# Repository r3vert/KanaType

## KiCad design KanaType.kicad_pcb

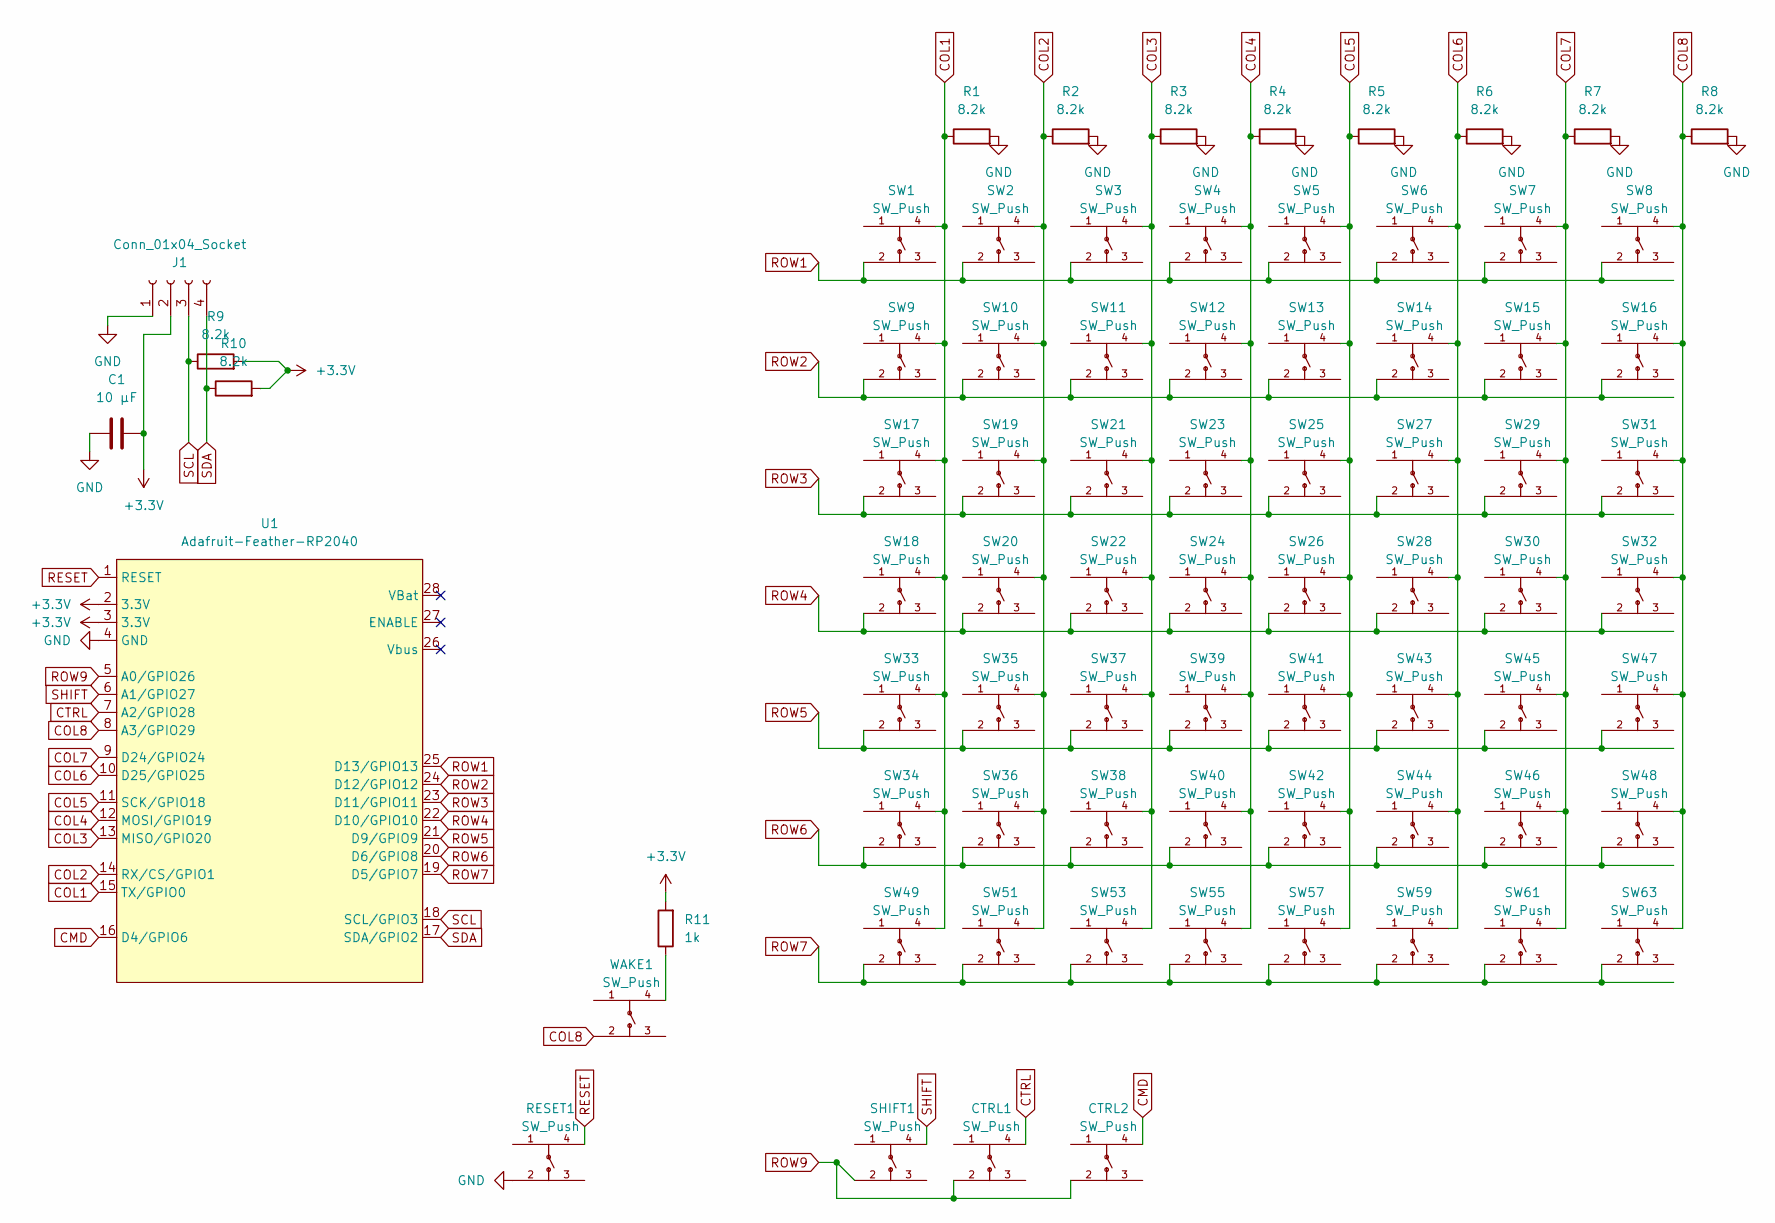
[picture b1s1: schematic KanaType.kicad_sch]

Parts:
C1: 10 μF; C_0805_2012Metric_Pad1.18x1.45mm_HandSolder
CTRL1, CTRL2: SW_Push; SW-SMD_4P-L4.2-W3.2-P2.15-LS4.6; LCSC C2910644
J1: Conn_01x04_Socket; PinSocket_1x04_P2.54mm_Vertical
R1, R2, R3, R4, R5, R6, R7, R8, R9, R10: 8.2k; R_0805_2012Metric_Pad1.20x1.40mm_HandSolder
R11: 1k; R_0805_2012Metric_Pad1.20x1.40mm_HandSolder
RESET1: SW_Push; SW-SMD_4P-L4.2-W3.2-P2.15-LS4.6; LCSC C2910644
SHIFT1: SW_Push; SW-SMD_4P-L4.2-W3.2-P2.15-LS4.6; LCSC C2910644
SW1, SW2, SW3, SW4, SW5, SW6, SW7, SW8, SW9, SW10, SW11, SW12, SW13, SW14, SW15, SW16, SW17, SW18, SW19, SW20, SW21, SW22, SW23, SW24, SW25, SW26, SW27, SW28, SW29, SW30, SW31, SW32, SW33, SW34, SW35, SW36, SW37, SW38, SW39, SW40, SW41, SW42, SW43, SW44, SW45, SW46, SW47, SW48, SW49, SW51, SW53, SW55, SW57, SW59, SW61, SW63: SW_Push; SW-SMD_4P-L4.2-W3.2-P2.15-LS4.6; LCSC C2910644
U1: Adafruit-Feather-RP2040; Adafruit_Feather
WAKE1: SW_Push; SW-SMD_4P-L4.2-W3.2-P2.15-LS4.6; LCSC C2910644

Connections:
+3.3V: C1.2, J1.2, R9.2, R10.2, R11.2, U1.2 (3.3V), U1.3 (3.3V)
CMD: CTRL2.4, U1.16 (D4/GPIO6)
COL1: R1.1, SW1.4, SW9.4, SW17.4, SW18.4, SW33.4, SW34.4, SW49.4, U1.15 (TX/GPIO0)
COL2: R2.1, SW2.4, SW10.4, SW19.4, SW20.4, SW35.4, SW36.4, SW51.4, U1.14 (RX/CS/GPIO1)
COL3: R3.1, SW3.4, SW11.4, SW21.4, SW22.4, SW37.4, SW38.4, SW53.4, U1.13 (MISO/GPIO20)
COL4: R4.1, SW4.4, SW12.4, SW23.4, SW24.4, SW39.4, SW40.4, SW55.4, U1.12 (MOSI/GPIO19)
COL5: R5.1, SW5.4, SW13.4, SW25.4, SW26.4, SW41.4, SW42.4, SW57.4, U1.11 (SCK/GPIO18)
COL6: R6.1, SW6.4, SW14.4, SW27.4, SW28.4, SW43.4, SW44.4, SW59.4, U1.10 (D25/GPIO25)
COL7: R7.1, SW7.4, SW15.4, SW29.4, SW30.4, SW45.4, SW46.4, SW61.4, U1.9 (D24/GPIO24)
COL8: R8.1, SW8.4, SW16.4, SW31.4, SW32.4, SW47.4, SW48.4, SW63.4, U1.8 (A3/GPIO29), WAKE1.2
CTRL: CTRL1.4, U1.7 (A2/GPIO28)
GND: C1.1, J1.1, R1.2, R2.2, R3.2, R4.2, R5.2, R6.2, R7.2, R8.2, RESET1.2, U1.4 (GND)
unnamed: R11.1, WAKE1.4
RESET: RESET1.4, U1.1 (RESET)
ROW1: SW1.2, SW2.2, SW3.2, SW4.2, SW5.2, SW6.2, SW7.2, SW8.2, U1.25 (D13/GPIO13)
ROW2: SW9.2, SW10.2, SW11.2, SW12.2, SW13.2, SW14.2, SW15.2, SW16.2, U1.24 (D12/GPIO12)
ROW3: SW17.2, SW19.2, SW21.2, SW23.2, SW25.2, SW27.2, SW29.2, SW31.2, U1.23 (D11/GPIO11)
ROW4: SW18.2, SW20.2, SW22.2, SW24.2, SW26.2, SW28.2, SW30.2, SW32.2, U1.22 (D10/GPIO10)
ROW5: SW33.2, SW35.2, SW37.2, SW39.2, SW41.2, SW43.2, SW45.2, SW47.2, U1.21 (D9/GPIO9)
ROW6: SW34.2, SW36.2, SW38.2, SW40.2, SW42.2, SW44.2, SW46.2, SW48.2, U1.20 (D6/GPIO8)
ROW7: SW49.2, SW51.2, SW53.2, SW55.2, SW57.2, SW59.2, SW61.2, SW63.2, U1.19 (D5/GPIO7)
ROW9: CTRL1.2, CTRL2.2, SHIFT1.2, U1.5 (A0/GPIO26)
SCL: J1.3, R9.1, U1.18 (SCL/GPIO3)
SDA: J1.4, R10.1, U1.17 (SDA/GPIO2)
SHIFT: SHIFT1.4, U1.6 (A1/GPIO27)

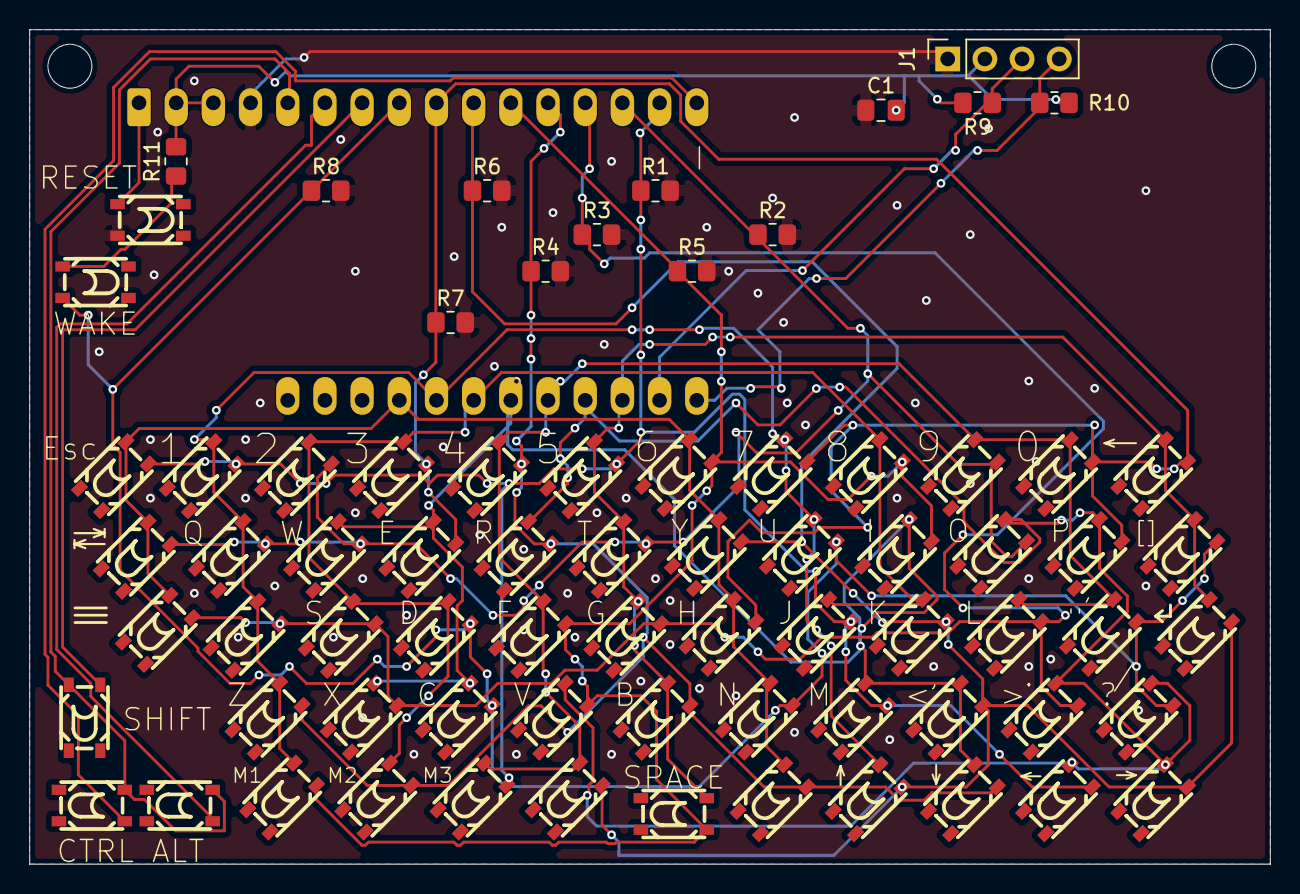
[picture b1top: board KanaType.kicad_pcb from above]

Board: 2 copper layers, 84.8 x 57.0 mm, 75 parts (1 on the bottom side), 25 nets.

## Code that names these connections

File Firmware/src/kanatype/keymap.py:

"""Physical keymap — single source of truth for BOTH the KMK keyboard app and
the app-platform MatrixInput driver (PLAN.md parity rule).

Grid derived from the PCB netlist + placement data (5 rows x 12 cols).
Each entry: (sw_ref, matrix_row 1-7, matrix_col 1-8, app_code, kmk_name)
  app_code: logical code for kanatype.input (None = no app meaning yet)
  kmk_name: attribute of kmk.keys.KC for USB keyboard mode

PROVISIONAL Preonic-style QWERTY — edit legends here and both worlds follow.
Hardware modifiers (CTRL1/CTRL2/SHIFT1) are off-matrix: see MOD_* below.
PURE PYTHON: no board imports (desktop renderer reads this file too).
"""

# Feather pin NAMES (resolved via getattr(board, name) on-device).
ROW_PIN_NAMES = ("D13", "D12", "D11", "D10", "D9", "D6", "D5")   # ROW1..ROW7
COL_PIN_NAMES = ("TX", "RX", "MISO", "MOSI", "SCK", "D25", "D24", "A3")  # COL1..COL8
ROW9_PIN_NAME = "A0"    # held LOW so modifiers read as ground-switched keys
# Hardware modifier keys by PCB net: A1=SHIFT1, A2=CTRL1, D4=CTRL2("CMD").
# USB functions remapped per user (2026-08): SHIFT1 key -> Alt,
# CTRL1 key -> Shift, CMD key -> Ctrl. No GUI key on this board.
MOD_PIN_NAMES = ("A1", "A2", "D4")
MOD_KMK_NAMES = ("LALT", "LSFT", "LCTL")

# MENU key (SW3, physically under Tab; was GRV). Holding it in keyboard mode
# returns to the launcher -- it replaced the Ctrl+Alt+Shift chord, which fired
# the instant all three went down and so could not be held deliberately.
# It sends NOTHING over USB ("NO"): the host repeats a held character, so a
# key you are meant to hold cannot also type one. In the apps it reads as
# "exit", the same code as ESC.
MENU_KEY = (1, 3)          # (matrix_row, matrix_col)

# User-assignable macro keys, left to right:
#     M1 = SW13 (2,5)   M2 = SW23 (3,4)   M3 = SW33 (5,1)   M4 = SW43 (5,6)
# Positions verified by matching silkscreen gr_text to footprint placement in
# KanaType.kicad_pcb. BOARD ERRATUM: the silkscreen prints M1/M2/M3 but has no
# legend for M4 (SW43) -- the key is unlabelled on the PCB, so the on-screen
# assignment list is the only place it is identified. Fix in v2.
# SW57 (7,5) is the spacebar and carries the SPACE legend, on its own.
# NOTE: LAYOUT still maps M2/M3/M4 as SPC -- they type a space today. That is
# corrected when the macro system lands.
MACRO_KEYS = ((2, 5), (3, 4), (5, 1), (5, 6))

# LAYER toggle: SW4, the unlabelled key right of the spacebar. Pressed (not
# held) it flips to a second layer where the macro keys become M5..M8 and the
# number row becomes function keys.
LAYER_KEY = (1, 4)

# What the second layer changes. Keyed by KMK NAME rather than by coordinate,
# so re-arranging LAYOUT moves these with it instead of silently pointing at
# whatever key inherited the position. The number row only has ten keys, so
# F11/F12 land on Q and W.
LAYER2_KMK = {
    "N1": "F1", "N2": "F2", "N3": "F3", "N4": "F4", "N5": "F5",
    "N6": "F6", "N7": "F7", "N8": "F8", "N9": "F9", "N0": "F10",
    "Q": "F11", "W": "F12",
}


def menu_matrix_index():
    """MENU_KEY as a KMK KeyMatrix flat index (same order as kmk_matrix_names)."""
    return (MENU_KEY[0] - 1) * 8 + (MENU_KEY[1] - 1)


def macro_matrix_indices():
    """MACRO_KEYS as KMK KeyMatrix flat indices, M1..M4 in order."""
    return [(r - 1) * 8 + (c - 1) for r, c in MACRO_KEYS]


def layer_matrix_index():
    """LAYER_KEY as a KMK KeyMatrix flat index."""
    return (LAYER_KEY[0] - 1) * 8 + (LAYER_KEY[1] - 1)


def layer2_overrides():
    """{flat index: KMK name} for every key the second layer replaces."""
    out = {}
    for row in LAYOUT:
        for _sw, r, c, _app, kmk in row:
            if kmk in LAYER2_KMK:
                out[(r - 1) * 8 + (c - 1)] = LAYER2_KMK[kmk]
    return out


def macro_label(rc):
    """'M1'..'M4' for a macro key's (row, col), else None."""
    try:
        return "M%d" % (MACRO_KEYS.index(tuple(rc)) + 1)
    except ValueError:
        return None

# 56 matrix keys, physical rows top-to-bottom, left-to-right.
LAYOUT = [
    [  # row 1 (top)
        ("SW1", 1, 1, "exit", "ESC"), ("SW9", 2, 1, "1", "N1"),
        ("SW19", 3, 2, "2", "N2"), ("SW29", 3, 7, "3", "N3"),
        ("SW39", 5, 4, "4", "N4"), ("SW49", 7, 1, "5", "N5"),
        ("SW5", 1, 5, "6", "N6"), ("SW15", 2, 7, "7", "N7"),
        ("SW25", 3, 5, "8", "N8"), ("SW35", 5, 2, "9", "N9"),
        ("SW45", 5, 7, "0", "N0"), ("SW61", 7, 7, "backspace", "BSPC"),
    ],
    [  # row 2
        ("SW2", 1, 2, None, "TAB"), ("SW10", 2, 2, "q", "Q"),
        ("SW20", 4, 2, "w", "W"), ("SW30", 4, 7, "e", "E"),
        ("SW40", 6, 4, "r", "R"), ("SW51", 7, 2, "t", "T"),
        ("SW6", 1, 6, "y", "Y"), ("SW16", 2, 8, "u", "U"),
        ("SW26", 4, 5, "i", "I"), ("SW36", 6, 2, "o", "O"),
        ("SW46", 6, 7, "p", "P"), ("SW63", 7, 8, "backspace", "DEL"),
    ],
    [  # row 3 (home)
        ("SW3", 1, 3, "exit", "NO"), ("SW11", 2, 3, "a", "A"),
        ("SW21", 3, 3, "s", "S"), ("SW31", 3, 8, "d", "D"),
        ("SW41", 5, 5, "f", "F"), ("SW53", 7, 3, "g", "G"),
        ("SW7", 1, 7, "h", "H"), ("SW17", 3, 1, "j", "J"),
        ("SW27", 3, 6, "k", "K"), ("SW37", 5, 3, "l", "L"),
        ("SW47", 5, 8, None, "SCLN"), ("SW59", 7, 6, "enter", "ENT"),
    ],
    [  # row 4 (CTRL1 hardware modifier sits physically leftmost)
        ("SW12", 2, 4, "z", "Z"), ("SW22", 4, 3, "x", "X"),
        ("SW32", 4, 8, "c", "C"), ("SW42", 6, 5, "v", "V"),
        ("SW55", 7, 4, "b", "B"), ("SW8", 1, 8, "n", "N"),
        ("SW18", 4, 1, "m", "M"), ("SW28", 4, 6, None, "COMM"),
        ("SW38", 6, 3, None, "DOT"), ("SW48", 6, 8, "hint", "SLSH"),
    ],
    [  # row 5 (bottom; CTRL2=CMD and SHIFT1 sit physically leftmost)
        # M1 still types "-": it is the ONLY minus on the board (the number
        # row has no MINS/EQL), so nulling it would leave no hyphen at all.
        ("SW13", 2, 5, None, "MINS"),
        # M2/M3/M4 were SPC, which contradicted the silkscreen -- they typed a
        # space. Unassigned until the macro system lands; SW57 is the spacebar.
        ("SW23", 3, 4, None, "NO"),
        ("SW33", 5, 1, None, "NO"), ("SW43", 5, 6, None, "NO"),
        ("SW57", 7, 5, "space", "SPC"),
        # LAYER toggle (right of space, unlabelled on the silkscreen). Was
        # RBRC -- the board's only "]", now gone. Sends nothing: it is a
        # toggle, and a key that also typed would fire on every press.
        ("SW4", 1, 4, "layer", "NO"),
        ("SW14", 2, 6, "up", "UP"), ("SW24", 4, 4, "down", "DOWN"),
        ("SW34", 6, 1, "left", "LEFT"), ("SW44", 6, 6, "right", "RGHT"),
    ],
]


def matrix_app_codes():
    """{(matrix_row, matrix_col): app_code} for the input driver."""
    return {(r, c): app for row in LAYOUT for _sw, r, c, app, _k in row}


def kmk_matrix_names():
    """56-entry list of KC names in KeyMatrix coord order (row-major
    ROW1..ROW7 x COL1..COL8) for the KMK keymap."""
    names = ["NO"] * 56
    for row in LAYOUT:
        for _sw, r, c, _app, kmk in row:
            names[(r - 1) * 8 + (c - 1)] = kmk
    return names
